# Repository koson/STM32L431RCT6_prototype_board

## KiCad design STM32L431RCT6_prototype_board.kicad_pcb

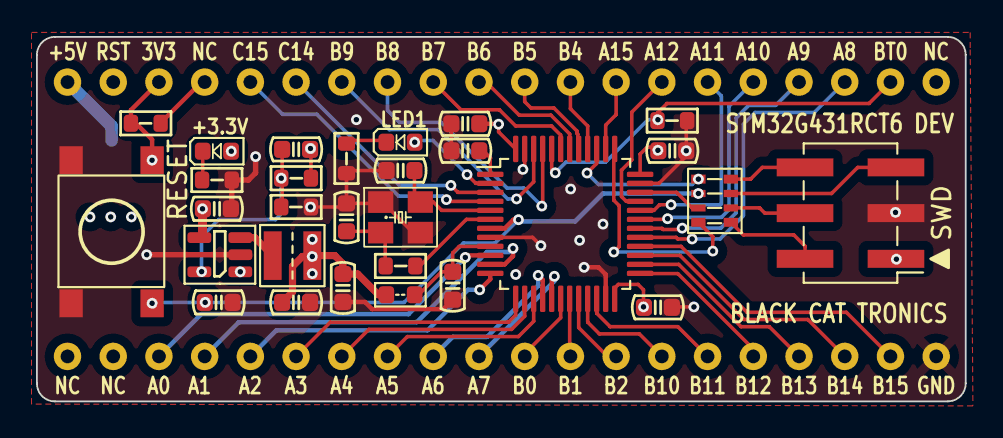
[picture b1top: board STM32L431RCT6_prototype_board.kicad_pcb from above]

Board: 4 copper layers, 51.6 x 20.2 mm, 31 parts (1 on the bottom side), 54 nets.

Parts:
C1, C2: 12pF; C_0603_1608Metric
C3, C4, C5, C6, C7, C8, C10: 100nF; C_0603_1608Metric
C9, C11, C12: 22uF; C_0603_1608Metric
F1: Fuse; Fuse_1812_4532Metric
FB1: BLM18PG300SN1D; L_0603_1608Metric
J1: SWD; PinHeader_2x03_P2.54mm_Vertical_SMD
J2: Conn_02x20_Counter_Clockwise; Socket_DIP-40_15.24mm_Conn
L1: 2.2uH/1.5A; L_Neosid_SMS-ME3015
LED1, LED2: RED; LED_0603_1608Metric
R1: 47R; R_0603_1608Metric
R2, R3: 10k; R_0603_1608Metric
R4: 220k; R_0603_1608Metric
R5: 49.9k; R_0603_1608Metric
R6, R7: 330; R_0603_1608Metric
RN1: 22R; R_Array_Convex_4x0603
S1: RESET; DTSM-6
U1: STM32L431CCTx; LQFP-48_7x7mm_P0.5mm
U2: SY8089; SOT-23-5
Y1: 8MHz; Crystal_SMD_3225-4Pin_3.2x2.5mm

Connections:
+3.3VA: C7.1, FB1.2, U1.9 (VDDA)
+3V3: C4.1, C5.1, C6.1, C10.1, C11.1, C12.1, FB1.1, J1.1, J2.37, L1.2, LED1.2 (A), R3.2, R4.1, U1.24 (VDD), U1.36 (VDD), U1.48 (VDD)
+5V: F1.1, J2.40
+BATT: C3.1, U1.1 (VBAT)
/+5.0V: C9.1, F1.2, U2.1 (EN), U2.4 (IN)
BOOT0: J2.22, R2.1, U1.44 (PH3)
GND: C1.2, C2.2, C3.2, C4.2, C5.2, C6.2, C7.2, C8.2, C9.2, C11.2, C12.2, J1.3, J2.20, R2.2, R5.2, R6.1, R7.1, S1.1, S1.2, U1.8 (VSSA), U1.23 (VSS), U1.35 (VSS), U1.47 (VSS), U2.2 (GND), Y1.2, Y1.4
HEART_BEAT: LED2.2 (A), U1.2 (PC13)
HSE_IN: C1.1, U1.5 (PH0), Y1.3
HSE_OUT: R1.1, U1.6 (PH1)
NRST: C8.1, J2.38, R3.1, RN1.6 (R3.2), S1.3, S1.4, U1.7 (NRST)
unnamed: C2.1, R1.2, Y1.1
unnamed: J1.2, RN1.1 (R1.1)
unnamed: J1.4, RN1.2 (R2.1)
unnamed: J1.5, RN1.3 (R3.1)
unnamed: J1.6, RN1.4 (R4.1)
unnamed: LED1.1 (K), R6.2
unnamed: LED2.1 (K), R7.2
unnamed: C10.2, R4.2, R5.1, U2.5 (FB)
unnamed: L1.1, U2.3 (LX)
PA0: J2.3, U1.10 (PA0)
PA1: J2.4, U1.11 (PA1)
PA2: J2.5, U1.12 (PA2)
PA3: J2.6, U1.13 (PA3)
PA4: J2.7, U1.14 (PA4)
PA5: J2.8, U1.15 (PA5)
PA6: J2.9, U1.16 (PA6)
PA7: J2.10, U1.17 (PA7)
PA8: J2.23, U1.29 (PA8)
PA9: J2.24, U1.30 (PA9)
PA10: J2.25, U1.31 (PA10)
PA11: J2.26, U1.32 (PA11)
PA12: J2.27, U1.33 (PA12)
PA15: J2.28, U1.38 (PA15)
PB0: J2.11, U1.18 (PB0)
PB1: J2.12, U1.19 (PB1)
PB2: J2.13, U1.20 (PB2)
PB4: J2.29, U1.40 (PB4)
PB5: J2.30, U1.41 (PB5)
PB6: J2.31, U1.42 (PB6)
PB7: J2.32, U1.43 (PB7)
PB8: J2.33, U1.45 (PB8)
PB9: J2.34, U1.46 (PB9)
PB10: J2.14, U1.21 (PB10)
PB11: J2.15, U1.22 (PB11)
PB12: J2.16, U1.25 (PB12)
PB13: J2.17, U1.26 (PB13)
PB14: J2.18, U1.27 (PB14)
PB15: J2.19, U1.28 (PB15)
PC14: J2.35, U1.3 (PC14)
PC15: J2.36, U1.4 (PC15)
SYS_JTCK-SWCLK: RN1.8 (R1.2), U1.37 (PA14)
SYS_JTDO-SWO: RN1.5 (R4.2), U1.39 (PB3)
SYS_JTMS-SWDIO: RN1.7 (R2.2), U1.34 (PA13)

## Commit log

2023-06-19 add gerber.
